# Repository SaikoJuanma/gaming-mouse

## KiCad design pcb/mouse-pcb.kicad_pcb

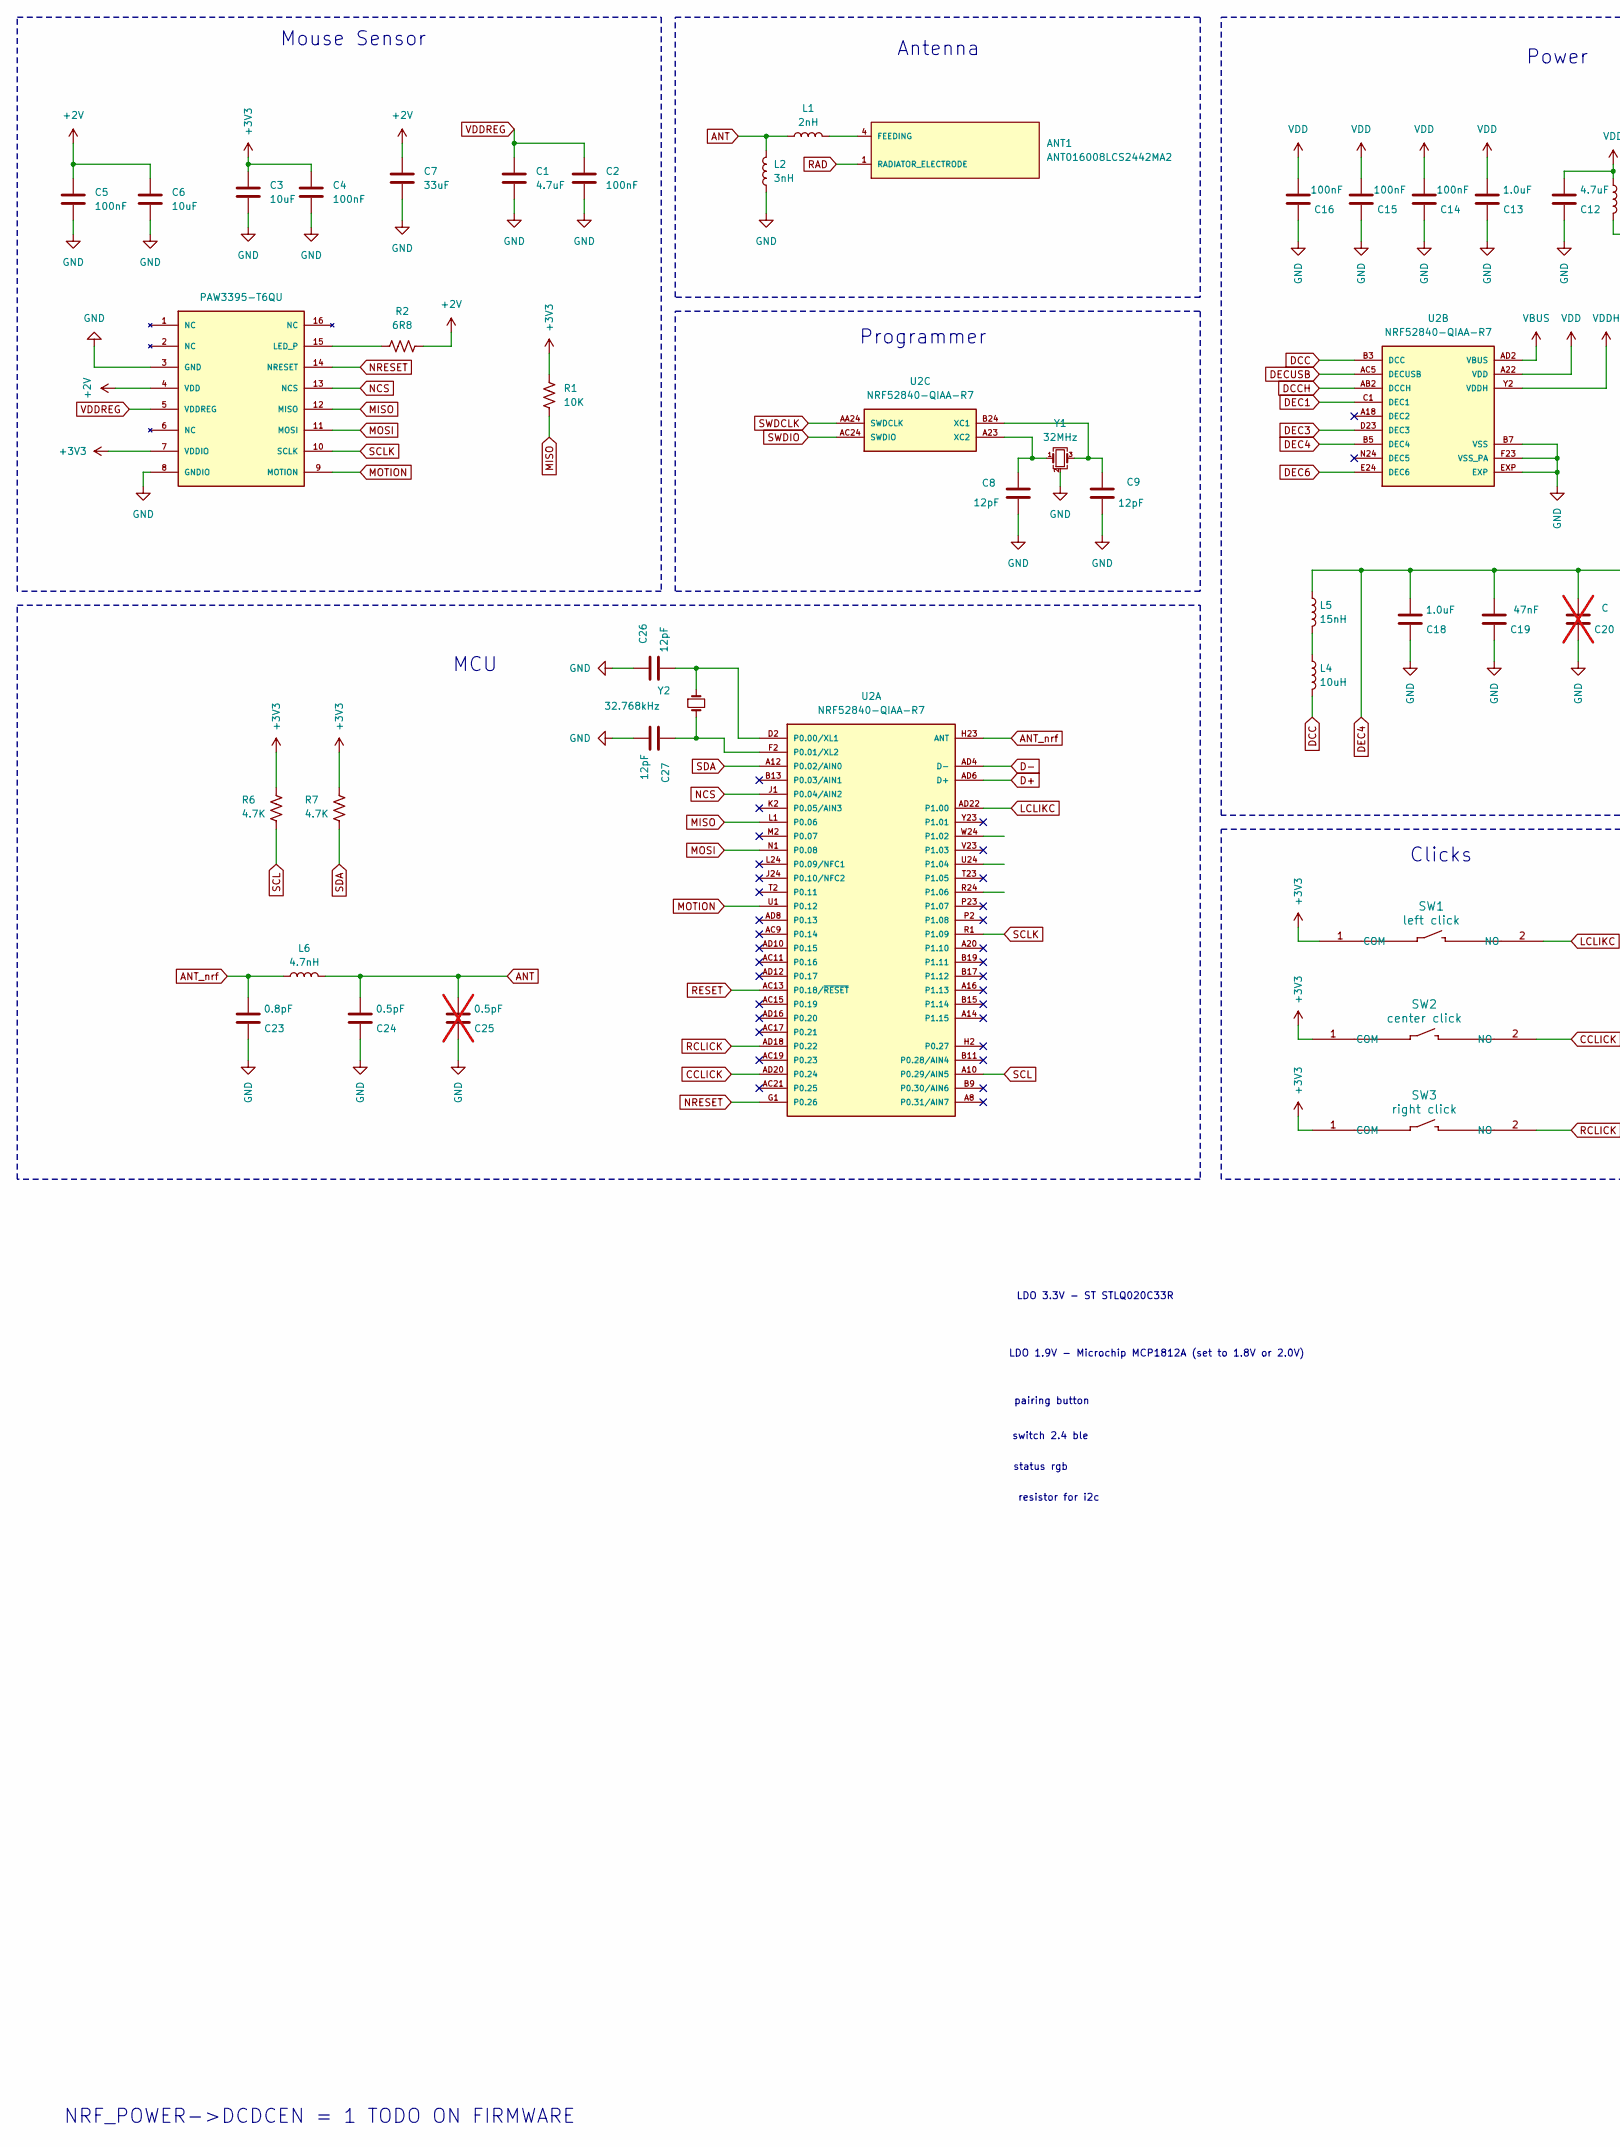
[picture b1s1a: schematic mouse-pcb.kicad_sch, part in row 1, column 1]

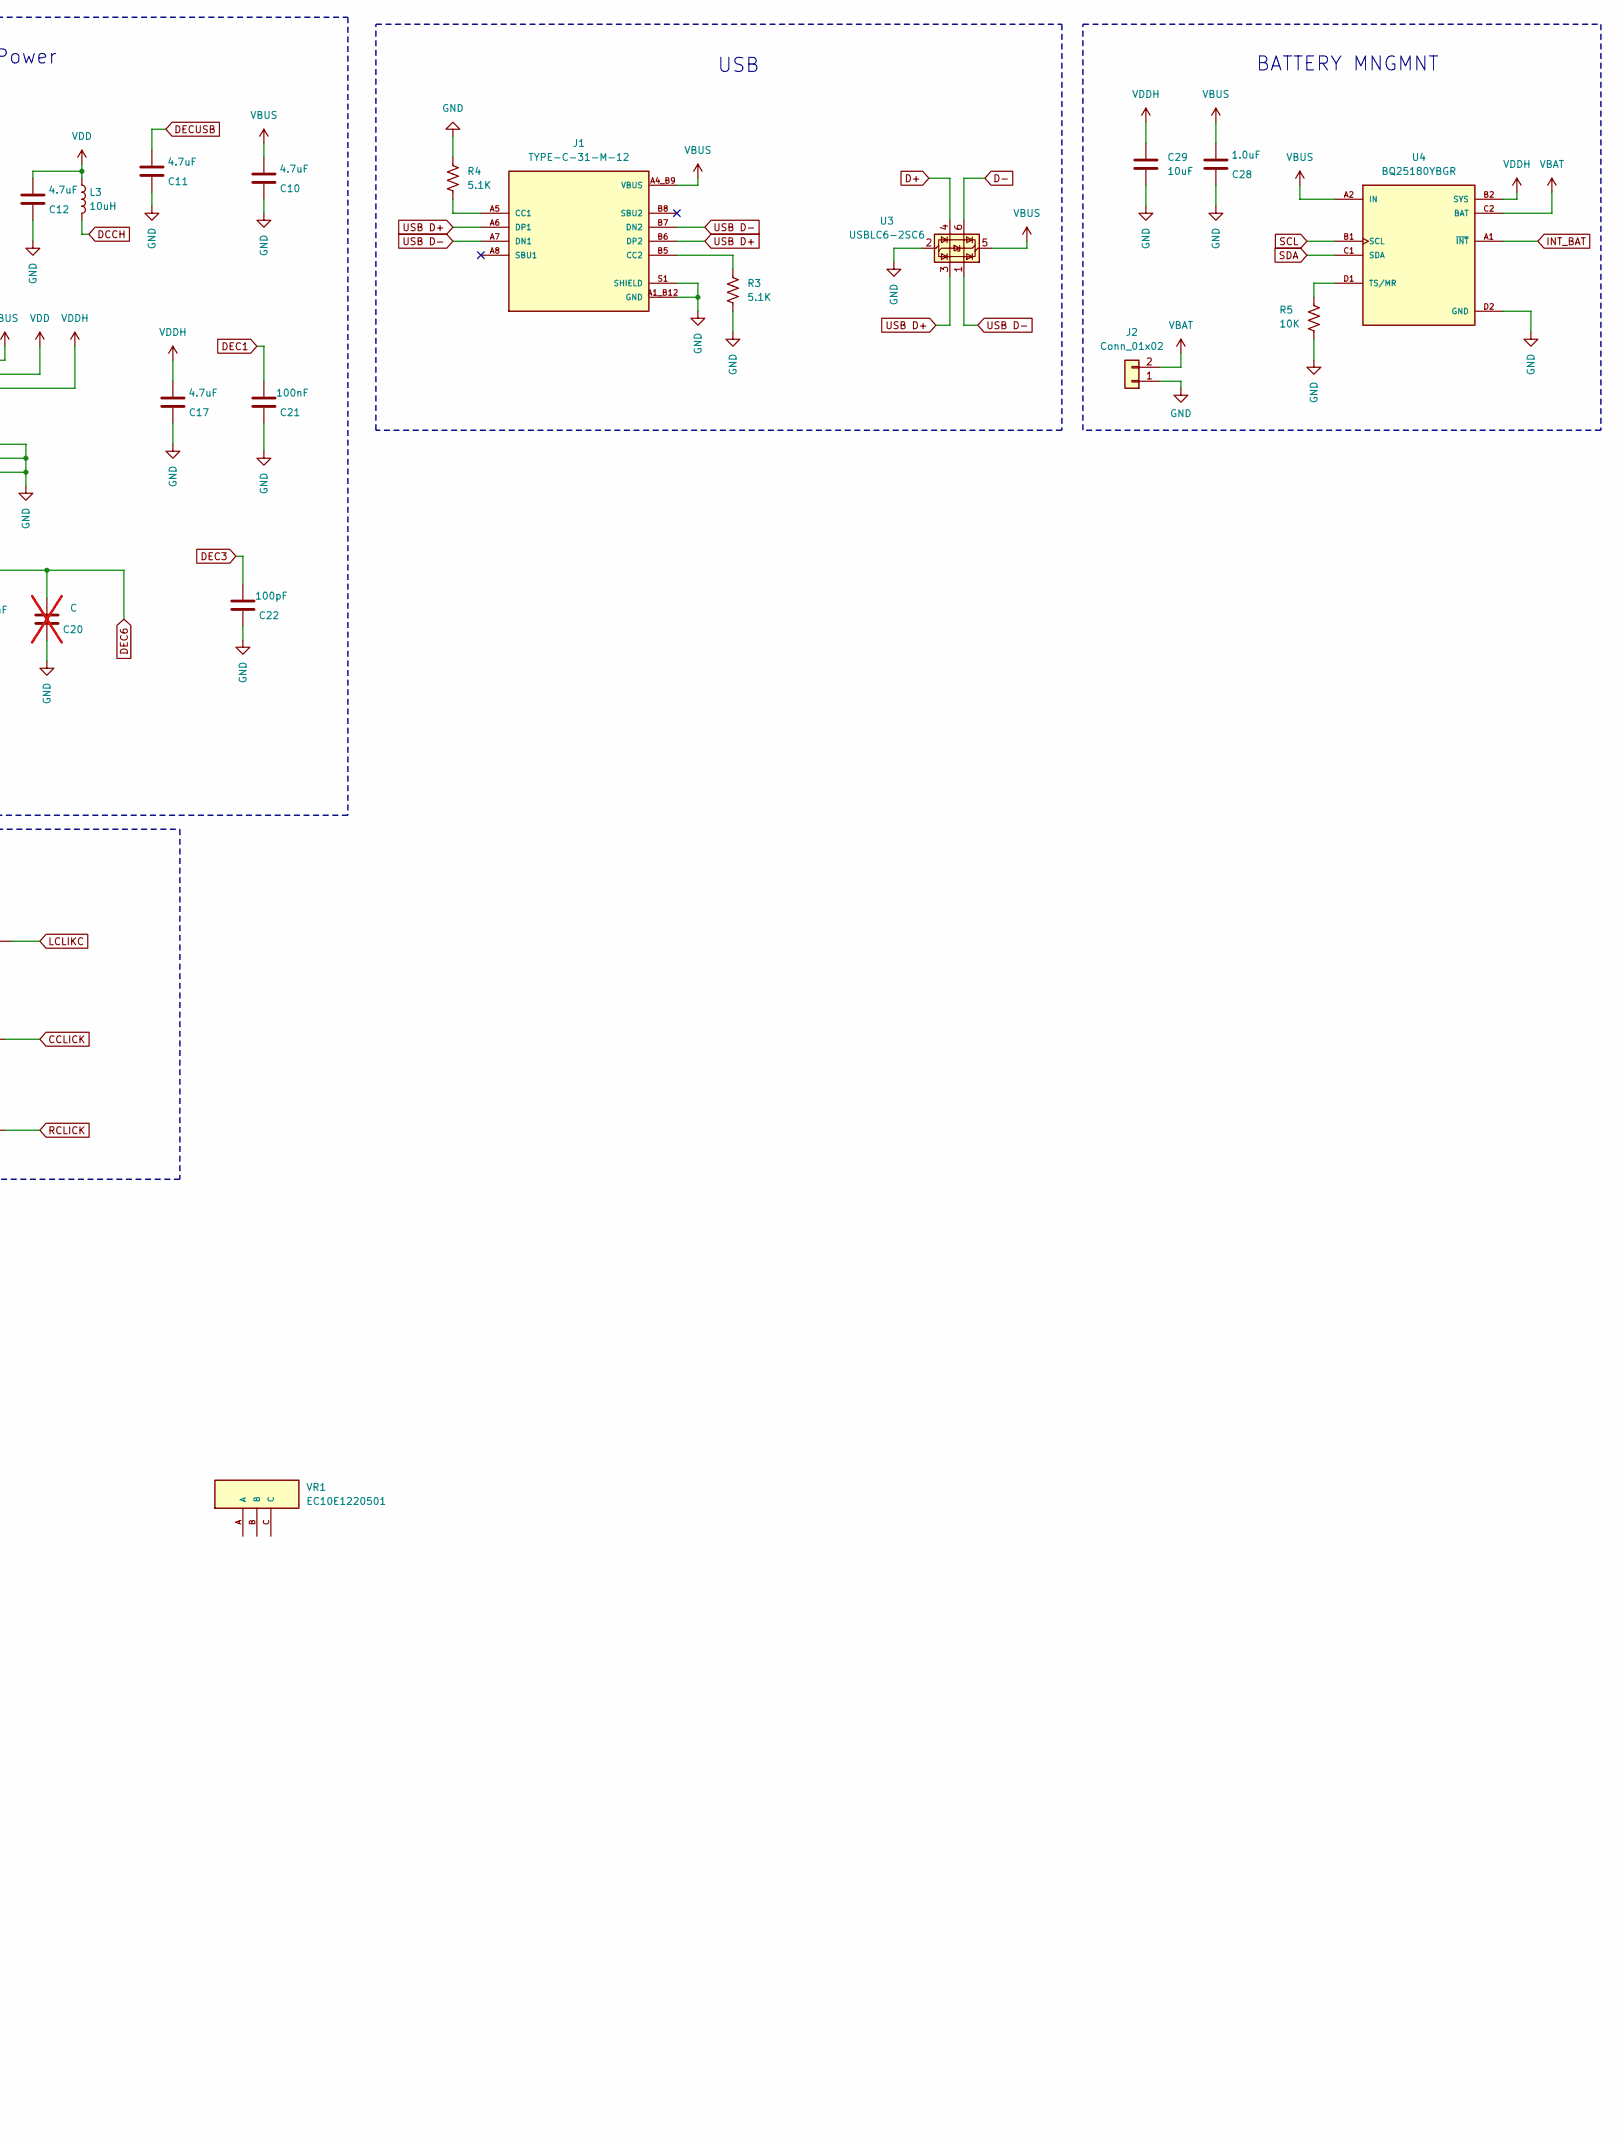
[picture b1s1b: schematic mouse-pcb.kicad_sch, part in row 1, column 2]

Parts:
ANT1: ANT016008LCS2442MA2; ANT_ANT016008LCS2442MA2; MPN ANT016008LCS2442MA2; LCSC_PART_NUMBER C209892
C1: 4.7uF; C_0805_2012Metric; MPN CL21A475KBQNNNE
C2, C4, C5: 100nF; C_0805_2012Metric; MPN CC0805KRX7R9BB104
C3, C6: 10uF; C_0805_2012Metric; MPN GRM21BR61H106KE43L
C7: 33uF; C_0805_2012Metric; MPN C2012X5R1A336MTJ00E
C8, C9, C26, C27: 12pF; C_0402_1005Metric; MPN TCC0402X7R123K500AT
C10, C11, C12, C17: 4.7uF; C_0402_1005Metric; MPN CL05A475MP5NRNC
C13, C18, C28: 1.0uF; C_0402_1005Metric; MPN CL05A105KP5NNNC
C14, C15, C16, C21: 100nF; C_0402_1005Metric; MPN CC0402KRX7R7BB104
C19: 47nF; C_0402_1005Metric; MPN CL05B473KB5VPNC
C20: C; C_0402_1005Metric; MPN CL05B473KB5VPNC; not fitted
C22: 100pF; C_0402_1005Metric; MPN GRM1555C1H101JA01D
C23: 0.8pF; C_0402_1005Metric; MPN GJM0335C1HR80WB01D
C24: 0.5pF; C_0201_0603Metric; MPN GJM0335C1ER50WB01D
C25: 0.5pF; C_0201_0603Metric; MPN GJM0335C1ER50WB01D; not fitted
C29: 10uF; C_0402_1005Metric; MPN CL05A106MP5NUNC
J1: TYPE-C-31-M-12; HRO_TYPE-C-31-M-12; PARTREV 2020.12.08; LCSC_PART_NUMBER C165948
J2: Conn_01x02; JST_SHL_SM02B-SHLS-TF_1x02-1MP_P1.00mm_Horizontal
L1: 2nH; L_0201_0603Metric; MPN LQP03TN2N0B02D; LCSC_PART_NUMBER C86125
L2: 3nH; L_0201_0603Metric; MPN LQP03HQ3N0B02D; LCSC_PART_NUMBER C2041469
L3, L4: 10uH; L_0402_1005Metric; MPN LQW15DN100M00D; LCSC_PART_NUMBER C910650
L5: 15nH; L_0402_1005Metric; MPN LQW15AN15NG00D; LCSC_PART_NUMBER C98055
L6: 4.7nH; L_0201_0603Metric; MPN LQP03TN4N7HZ2D; LCSC_PART_NUMBER C6980459
R1: 10K; C_0805_2012Metric; MPN RC0805FR-0710KL; LCSC_PART_NUMBER C84376
R2: 6R8; R_0805_2012Metric; MPN 0805 ±1% 6Ω8; LCSC_PART_NUMBER C2889463
R3, R4: 5.1K; C_0805_2012Metric; MPN HoAR0805-1/8W-5.1KR-0.1%-TCR25; LCSC_PART_NUMBER C2912598
R5: 10K; C_0402_1005Metric; MPN C60490; LCSC_PART_NUMBER C2912598
R6, R7: 4.7K; C_0402_1005Metric; MPN RC0402FR-074K7L; LCSC_PART_NUMBER C105871
SW1: left click; SW_D2FC_OMR; MPN D2FC-F-7N(20M); LCSC_PART_NUMBER C5157566
SW2: center click; SW_D2FC_OMR; MPN D2FC-F-7N(20M); LCSC_PART_NUMBER C5157566
SW3: right click; SW_D2FC_OMR; MPN D2FC-F-7N(20M); LCSC_PART_NUMBER C5157566
U1: PAW3395-T6QU; paw3395; MPN PAW3395DM-T6QU; LCSC_PART_NUMBER C41346211
U2: NRF52840-QIAA-R7; NORDIC_NRF52840-QIAA-R7; PARTREV 1.2; LCSC_PART_NUMBER C190794
U3: USBLC6-2SC6; SOT-23-6; MPN USBLC6-2SC6
U4: BQ25180YBGR; IC_BQ25180YBGR; PARTREV C; LCSC_PART_NUMBER C3682423
VR1: EC10E1220501; TRIM_EC10E1220501; MPN EC10E1220501; LCSC_PART_NUMBER C160889
Y1: 32MHz; Crystal_SMD_WE_IQXC-42-4Pin_2.0x1.6mm; MPN XL7EL89COI-111YLC-32M; LCSC_PART_NUMBER C2965584
Y2: 32.768kHz; Crystal_SMD_3215-2Pin_3.2x1.5mm; MPN Q13FC13500004; LCSC_PART_NUMBER C32346

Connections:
+2V: C5.1, C6.1, C7.1, R2.2, U1.4 (VDD)
+3V3: C3.1, C4.1, R1.1, R6.1, R7.1, SW1.1 (COM), SW2.1 (COM), SW3.1 (COM), U1.7 (VDDIO)
ANT: C24.2, C25.2, L1.1, L2.2, L6.2
ANT_nrf: C23.2, L6.1, U2.H23 (ANT)
CCLICK: SW2.2 (NO), U2.AD20 (P0.24)
D+: U2.AD6 (D+), U3.4 (I/O2)
D-: U2.AD4 (D-), U3.6 (I/O1)
DCC: L4.2, U2.B3 (DCC)
DCCH: L3.2, U2.AB2 (DCCH)
DEC1: C21.2, U2.C1 (DEC1)
DEC3: C22.2, U2.D23 (DEC3)
DEC4: C18.2, C19.2, C20.2, L5.1, U2.B5 (DEC4), U2.E24 (DEC6)
DECUSB: C11.2, U2.AC5 (DECUSB)
GND: C1.2, C2.2, C3.2, C4.2, C5.2, C6.2, C7.2, C8.2, C9.2, C10.1, C11.1, C12.1, C13.1, C14.1, C15.1, C16.1, C17.1, C18.1, C19.1, C20.1, C21.1, C22.1, C23.1, C24.1, C25.1, C26.1, C27.2, C28.1, C29.2, J1.A1_B12 (GND), J1.B1_A12 (GND), J1.S1 (SHIELD), J1.S2 (SHIELD), J1.S3 (SHIELD), J1.S4 (SHIELD), J2.1, L2.1, R3.2, R4.1, R5.2, U1.3 (GND), U1.8 (GNDIO), U2.B7 (VSS), U2.EXP, U2.F23 (VSS_PA), U3.2 (GND), U4.D2 (GND), Y1.2 (G), Y1.4 (G)
INT_BAT: U4.A1 (~INT)
LCLIKC: SW1.2 (NO), U2.AD22 (P1.00)
MISO: R1.2, U1.12 (MISO), U2.L1 (P0.06)
MOSI: U1.11 (MOSI), U2.N1 (P0.08)
MOTION: U1.9 (MOTION), U2.U1 (P0.12)
NCS: U1.13 (NCS), U2.J1 (P0.04/AIN2)
NRESET: U1.14 (NRESET), U2.G1 (P0.26)
unnamed: ANT1.4 (FEEDING), L1.2
unnamed: J1.A5 (CC1), R4.2
unnamed: J1.B5 (CC2), R3.1
unnamed: L4.1, L5.2
unnamed: R2.1, U1.15 (LED_P)
unnamed: C26.2, U2.D2 (P0.00/XL1), Y2.1
unnamed: C27.1, U2.F2 (P0.01/XL2), Y2.2
unnamed: C9.1, U2.B24 (XC1), Y1.3
unnamed: C8.1, U2.A23 (XC2), Y1.1
unnamed: R5.1, U4.D1 (TS/MR)
RAD: ANT1.1 (RADIATOR_ELECTRODE)
RCLICK: SW3.2 (NO), U2.AD18 (P0.22)
RESET: U2.AC13 (P0.18/~RESET)
SCL: R6.2, U2.A10 (P0.29/AIN5), U4.B1 (SCL)
SCLK: U1.10 (SCLK), U2.R1 (P1.09)
SDA: R7.2, U2.A12 (P0.02/AIN0), U4.C1 (SDA)
SWDCLK: U2.AA24 (SWDCLK)
SWDIO: U2.AC24 (SWDIO)
USB D+: J1.A6 (DP1), J1.B6 (DP2), U3.3 (I/O2)
USB D-: J1.A7 (DN1), J1.B7 (DN2), U3.1 (I/O1)
VBAT: J2.2, U4.C2 (BAT)
VBUS: C10.2, C28.2, J1.A4_B9 (VBUS), J1.B4_A9 (VBUS), U2.AD2 (VBUS), U3.5 (VBUS), U4.A2 (IN)
VDD: C12.2, C13.2, C14.2, C15.2, C16.2, L3.1, U2.A22 (VDD), U2.AD14 (VDD), U2.AD23 (VDD), U2.B1 (VDD), U2.W1 (VDD)
VDDH: C17.2, C29.1, U2.Y2 (VDDH), U4.B2 (SYS)
VDDREG: C1.1, C2.1, U1.5 (VDDREG)

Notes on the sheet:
BATTERY MNGMNT
LDO 1.9V - Microchip MCP1812A (set to 1.8V or 2.0V)
MCU
Clicks
Antenna
Mouse Sensor
status rgb
Programmer
LDO 3.3V - ST STLQ020C33R
Power
USB
switch 2.4 ble
pairing button
NRF_POWER->DCDCEN = 1 TODO ON FIRMWARE
resistor for i2c

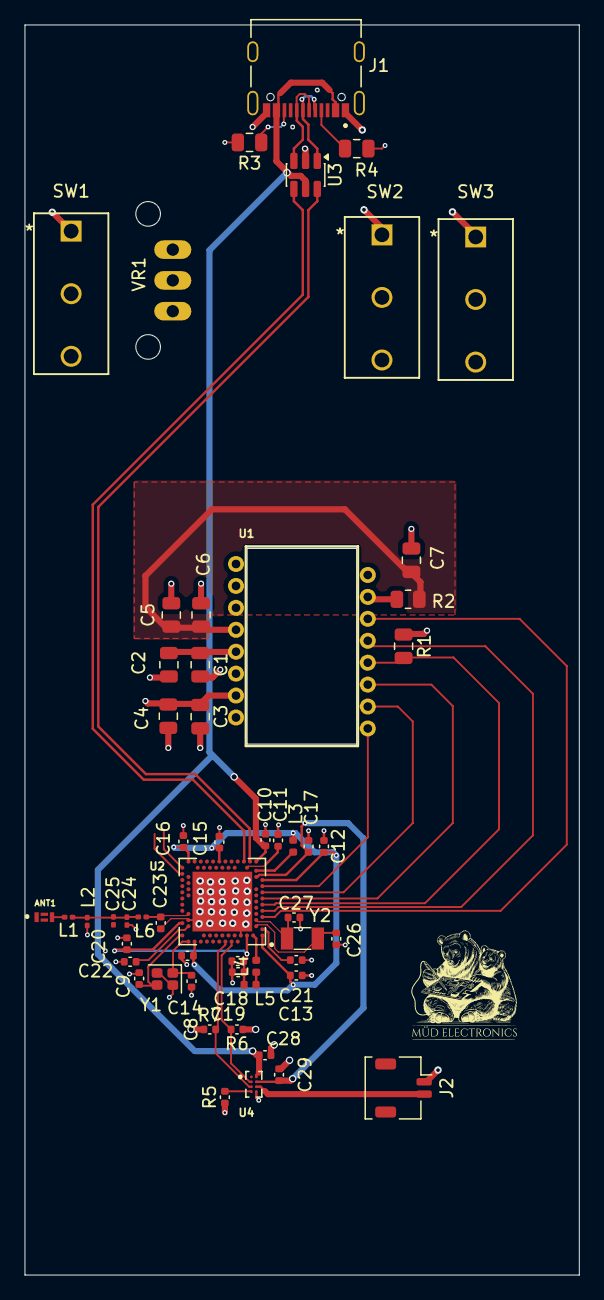
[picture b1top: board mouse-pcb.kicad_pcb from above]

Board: 4 copper layers, 45.0 x 101.5 mm, 55 parts (0 on the bottom side), 41 nets.

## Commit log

2026-03-12 chore: creation of the repo
2026-03-12 chore: creation of the first kicad files
2026-03-13 feat: gitignore, and pmw3395 added
2026-03-13 chore: add nrf54l15 to the directory
2026-03-16 feat: add new library for the mouse
2026-03-16 feat: add more components to the library
2026-03-18 feat: adding all the passive for mouse
2026-03-19 feat: all connections for the mouse sensor done
2026-03-19 fix: improve the tracks and zones
2026-03-26 feat: 10mm logo added to library and pcb
2026-03-27 feat: common circuits for chip, antenna remaining
2026-03-29 feat: new micro, and antenna
2026-04-01 ci: ci implemented for kicad
2026-04-02 feat: all micro circuits added
2026-04-06 feat: impedance calcualated
    JLC04161H-3313(finished thicknes1.56mm+-10%
    50 ohm 6.16 mil width (antenna)
    90 ohm 4.4 mil width 4.0 mil spacing (differential pair)
2026-04-06 feat: 3d model for mcu added
2026-04-06 feat: usblc6 added
2026-04-07 feat: battery management added, mcu circuits are ready
2026-04-07 chore: rounding edges
